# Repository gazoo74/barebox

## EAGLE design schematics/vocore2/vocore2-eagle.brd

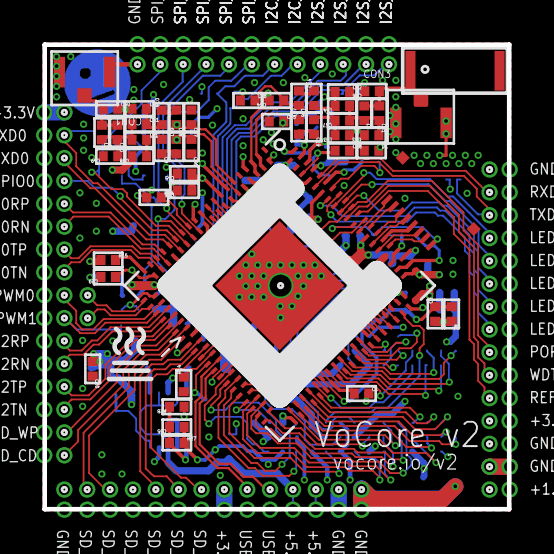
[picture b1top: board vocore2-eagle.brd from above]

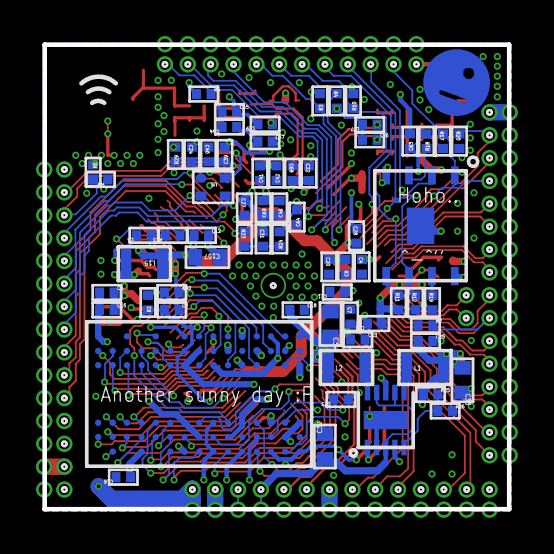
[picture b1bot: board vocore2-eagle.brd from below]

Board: 2 copper layers, 25.8 x 25.8 mm, 177 parts (68 on the bottom side), 129 nets.

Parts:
C1, C2, C3, C4, C5, C6, C7, C8, C9, C10, C11, C12, C13, C14, C15, C16, C18, C19, C20, C21, C22, C23, C24, C25, C27, C28, C29, C30, C31, C35, C36, C37, C38, C39, C40, C41, C42, C43, C44, C45, C46, C47, C48, C49, C50, C51, C52, C53, C54, C55, C56, C57, C60, C61, C63, C64, C65, C68, C69: 0402; 0402_1PRIMARY
C32, C33, C34, C107: 0603; 0603_1PRIMARY
CON1, CON3: SMA$2F$UFLR; SMA$2F$UFLR_1PRIMARY
CON2: 5020; 5020_1PRIMARY
D1: 0402; 0402_1PRIMARY
L1, L2, L15: 0806; 0806_1PRIMARY
L3, L5, L26, L27, L28, L29, L48, L49, L50, L51, L53, L54, L56, L57: 0402; 0402_1PRIMARY
LX01, LX02: PORT_1PIN_DECAL; PORT_1PIN_DECAL_1PRIMARY
PB00, PB01, PB02, PB03, PB04, PB05, PB06, PB07, PB08, PB09, PB10, PB11, PB12, PB13: PORT_1P5PIN_DECAL; PORT_1P5PIN_DECAL_1PRIMARY
PL00, PL01, PL02, PL03, PL04, PL05, PL06, PL07, PL08, PL09, PL10, PL11, PL12, PL13, PL14, PL15: PORT_1P5PIN_DECAL; PORT_1P5PIN_DECAL_1PRIMARY
PM00: PORT_1PIN_DECALDA; PORT_1PIN_DECALDA_1PRIMARY
PR00, PR01, PR02, PR03, PR04, PR05, PR06, PR07, PR08, PR09, PR10, PR11, PR12, PR13, PR14: PORT_1P5PIN_DECAL; PORT_1P5PIN_DECAL_1PRIMARY
PT00, PT01, PT02, PT03, PT04, PT05, PT06, PT07, PT08, PT09, PT10, PT11: PORT_1P5PIN_DECAL; PORT_1P5PIN_DECAL_1PRIMARY
R1, R2, R3, R4, R5, R6, R7, R9, R10, R11, R12, R13, R14, R15, R16, R17, R18, R19, R20, R23, R24, R25, R26, R27, R28, R29, R30: 0402; 0402_1PRIMARY
U1: MT7628AN$2F$DRQFN156$2F$SMD$2F$P0.5$2F$12X12; MT7628AN$2F$DRQFN156$2F$SMD$31PRIMARY
U2: BGA-84; BGA-84_1PRIMARY
U3: GD25Q128CW; GD25Q128CW_1PRIMARY
U4: TPS62410DRCR; TPS62410DRCR_1PRIMARY
U5: XTAL2520; XTAL2520_1PRIMARY
U8$2F$NC$2F$HIDE: FH19SC-8S-0.5SH; FH19SC-8S-0.5SH_1PRIMARY

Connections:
$$$4985: C10.2, C51.1, L50.1
$$$5344: C49.2, C51.2, C60.1, L3.1, L51.2
$$$5504: C14.2, C52.2, L54.1
$$$5505: C53.2, C57.2, C61.1, L5.1, L54.2
$$$21554: C2.2, C3.1, R1.2, R2.1, U1.90, U1.104, U2.50
$$$26111: C50.2, C60.2, CON1.1, L3.2
$$$26247: C9.1, L49.2
$$$26315: C10.1, L48.2
$$$26342: C56.2, C61.2, CON2.2, CON3.1, L5.2
$$$26483: C14.1, L56.2
$$$26503: C19.1, L57.2
$$$30241: C9.2, C48.2, L51.1
$$$30244: C19.2, C57.1, L53.1
+1.2V: C1.2, C7.2, C8.2, C11.2, C12.2, C13.2, C20.1, C27.2, C28.2, C107.2, L15.1, U1.22, U1.58, U1.89, U1.91, U1.122, U1.131, U1.145
+1.8V: C2.1, C6.2, C15.2, C16.2, C18.2, C34.1, C35.2, C41.2, C42.2, C43.2, C44.2, C45.2, C46.2, C47.2, C69.2, L2.1, PR14.1, PR14.2, R2.2, R27.1, R30.2, U1.15, U1.79, U1.98, U1.116, U1.149, U1.154, U1.155, U2.1, U2.6, U2.13, U2.15, U2.16, U2.18, U2.25, U2.30, U2.37, U2.39, U2.40, U2.42, U2.49, U2.54, U2.69, U2.80
+3.3V: C4.1, C5.2, C21.1, C22.2, C23.2, C24.2, C25.2, C29.2, C30.2, C33.2, C39.1, C40.2, C63.1, C64.2, C65.1, C68.2, L1.2, L26.2, L27.1, L28.2, L29.1, PB07.1, PB07.2, PL00.1, PL00.2, PR11.1, PR11.2, R3.2, R4.2, R9.2, R12.2, R13.1, R17.2, R18.2, R19.2, R24.2, R25.2, U1.8, U1.14, U1.23, U1.32, U1.38, U1.41, U1.53, U1.60, U1.117, U1.123, U1.124, U1.134, U1.146, U1.150, U3.8, U4.4
+5V: C32.2, PB12.1, PB12.2, PB13.1, PB13.2, U4.3, U4.7, U4.9
DCDC_ADJ2: C35.1, R27.2, R28.1, U4.1
DCDC_DEF1: R25.1, R26.2, U4.5
DCDC_SW1: L1.1, U4.6
DCDC_SW2: L2.2, U4.10
DDR2_A0: U1.80, U2.68
DDR2_A1: U1.88, U2.66
DDR2_A2: U1.87, U2.67
DDR2_A3: U1.97, U2.71
DDR2_A4: U1.82, U2.74
DDR2_A5: U1.93, U2.72
DDR2_A6: U1.86, U2.73
DDR2_A7: U1.95, U2.75
DDR2_A8: U1.84, U2.78
DDR2_A9: U1.94, U2.76
DDR2_A10: U1.92, U2.65
DDR2_A11: U1.85, U2.77
DDR2_A12: U1.96, U2.81
DDR2_A13: U1.83, U2.84
DDR2_BA0: U1.100, U2.61
DDR2_BA1: U1.99, U2.62
DDR2_BA2: U1.101, U2.60
DDR2_CAS: U1.75, U2.63
DDR2_CKE: U1.103, U2.55
DDR2_CLK: U1.77, U2.53
DDR2_CLKN: U1.76, U2.58
DDR2_CS: U1.78, U2.64
DDR2_LDM: U1.108, U2.33
DDR2_LDQS: U1.113, U2.34
DDR2_MD0: U1.71, U2.41
DDR2_MD1: U1.107, U2.38
DDR2_MD2: U1.69, U2.46
DDR2_MD3: U1.105, U2.45
DDR2_MD4: U1.106, U2.43
DDR2_MD5: U1.73, U2.48
DDR2_MD6: U1.109, U2.31
DDR2_MD7: U1.70, U2.36
DDR2_MD8: U1.66, U2.17
DDR2_MD9: U1.112, U2.14
DDR2_MD10: U1.68, U2.22
DDR2_MD11: U1.110, U2.21
DDR2_MD12: U1.111, U2.19
DDR2_MD13: U1.67, U2.24
DDR2_MD14: U1.114, U2.7
DDR2_MD15: U1.65, U2.12
DDR2_ODT: U1.74, U2.59
DDR2_RAS: U1.81, U2.57
DDR2_UDM: U1.64, U2.9
DDR2_UDQS: U1.72, U2.10
DDR2_WE: U1.102, U2.56
DDRLDO18V: R30.1, U1.125
EPHY_VRT: R15.1, U1.39
FLASH_HOLD: R19.1, U3.7
FLASH_WP: R18.1, U3.3
GND: C1.1, C3.2, C4.2, C5.1, C6.1, C7.1, C8.1, C11.1, C12.1, C13.1, C15.1, C16.1, C18.1, C20.2, C21.2, C22.1, C23.1, C24.1, C25.1, C27.1, C28.1, C29.1, C30.1, C31.1, C32.1, C33.1, C34.2, C36.1, C37.2, C38.1, C39.2, C40.1, C41.1, C42.1, C43.1, C44.1, C45.1, C46.1, C47.1, C48.1, C49.1, C50.1, C52.1, C53.1, C54.1, C55.2, C56.1, C63.2, C64.1, C65.2, C68.1, C69.1, C107.1, CON1.2, CON1.3, CON3.2, CON3.3, D1.2, L50.2, L53.2, PB00.1, PB00.2, PB10.1, PB10.2, PB11.1, PB11.2, PM00.1, PR00.1, PR00.2, PR12.1, PR12.2, PR13.1, PR13.2, PT00.1, PT00.2, R1.1, R5.2, R6.2, R7.2, R10.2, R11.2, R14.2, R15.2, R20.2, R26.1, R28.2, U1.1, U1.2, U1.7, U1.10, U1.13, U1.63, U1.115, U1.120, U1.121, U1.128, U1.152, U1.156, U1.157, U2.3, U2.4, U2.8, U2.11, U2.20, U2.23, U2.27, U2.28, U2.32, U2.35, U2.44, U2.47, U2.51, U2.52, U2.70, U2.79, U3.4, U3.9, U4.2, U4.8, U4.11, U5.2, U5.3, U5.4
GPIO0: PL03.1, PL03.2, U1.29
I2C_CLK: PT07.1, PT07.2, R3.1, U1.20
I2C_SD: PT06.1, PT06.2, R4.1, U1.21
I2S_CLK: PT08.1, PT08.2, U1.19
I2S_SDI: PT10.1, PT10.2, U1.16
I2S_SDO: PT11.1, PT11.2, R5.1, U1.17
I2S_WS: PT09.1, PT09.2, U1.18
LED0: PR06.1, PR06.2, U1.143
LED1: PR07.1, PR07.2, U1.142
LED2: PR03.1, PR03.2, U1.141
LED3: PR04.1, PR04.2, U1.140
LED4: PR05.1, PR05.2, U1.139
LXBK: L15.2, U1.118, U1.119
MDI_P0RN: PL05.1, PL05.2, U1.34
MDI_P0RP: PL04.1, PL04.2, U1.33
MDI_P0TN: PL07.1, PL07.2, U1.36
MDI_P0TP: PL06.1, PL06.2, U1.35
MDI_P1RN: PL09.1, PL09.2, R7.1, U1.44
MDI_P1RP: PL08.1, PL08.2, U1.43
MDI_P1TN: LX02.1, U1.42
MDI_P1TP: LX01.1, U1.40
MDI_P2RN: PL11.1, PL11.2, U1.46
MDI_P2RP: PL10.1, PL10.2, U1.45
MDI_P2TN: PL13.1, PL13.2, U1.48
MDI_P2TP: PL12.1, PL12.2, U1.47
MDI_P3RN: PB02.1, PB02.2, U1.52
MDI_P3RP: PB01.1, PB01.2, U1.51
MDI_P3TN: PL15.1, PL15.2, U1.50
MDI_P3TP: PL14.1, PL14.2, U1.49
MDI_P4RN: PB04.1, PB04.2, U1.55
MDI_P4RP: PB03.1, PB03.2, U1.54
MDI_P4TN: PB06.1, PB06.2, U1.57
MDI_P4TP: PB05.1, PB05.2, U1.56
PERST_N: R13.2, U1.135
PORST: PR08.1, PR08.2, R23.1, U1.138
PORST_M: C31.2, R23.2, R24.1
REFCLK: PR10.1, PR10.2, U1.136
SPI_CLK: PT02.1, PT02.2, R12.1, R16.2, U3.6
SPI_CLK_O: R16.1, U1.25
SPI_CS0: PT01.1, PT01.2, R17.1, U1.28, U3.1
SPI_CS1: PT05.1, PT05.2, R10.1, U1.24
SPI_MISO: PT03.1, PT03.2, U1.26, U3.2
SPI_MOSI: PT04.1, PT04.2, R11.1, U1.27, U3.5
UART_RXD0: PL02.1, PL02.2, U1.31
UART_RXD1: PR01.1, PR01.2, U1.148
UART_TXD0: PL01.1, PL01.2, R20.1, U1.30
UART_TXD1: PR02.1, PR02.2, R6.1, R9.1, U1.147
USB_DM: PB09.1, PB09.2, U1.62
USB_DP: PB08.1, PB08.2, U1.61
USB_VRT: R14.1, U1.59
WDTRST: PR09.1, PR09.2, U1.137
WF0_RFION: C55.1, L29.2, L57.1, U1.3, U1.4
WF0_RFIOP: C54.2, L28.1, L56.1, U1.5, U1.6
WF1_RFION: C37.1, L27.2, L48.1, U1.11
WF1_RFIOP: C36.2, L26.1, L49.1, U1.12
WLED_M: D1.1, R29.2
WLED_O: R29.1, U1.144
XTALIN: C38.2, U1.151, U5.1

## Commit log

2018-10-17 MIPS: add Vonger VoCore2 board
    This board is based on Mediatek mt7628an SoC.
2018-10-17 MIPS: start.S: split ERL reset from mips_disable_interrupts
    Currently, we cannot restart barebox from a bootloader. In macro
    mips_disable_interrupts we try to mask ST0_ERL. This flag is set by the
    CPU after a reset.
    When this Error Level flag is not set and we try to mask it, barebox
    stops to run without any further traces.
    To avoid such situation, we mask this flag in a dedicated macro.
2018-10-17 debug_ll: add GETC_LL and TSTC_LL functions
2018-10-17 MIPS: mt7628: register debug-ll console
2018-10-17 MIPS: mt7628: add uartlite
2018-10-17 datasheet: add vocore2 documents
    Downloaded from here[1] and there[2].
    [1]: http://vonger.cn/misc/vocore2/datasheet.zip
    [2]: http://vonger.cn/misc/vocore2/source.zip
2018-10-17 MIPS: mt7628: make debug ll uartlite selectable
2018-10-17 Add low-level ns16550 serial driver
2018-10-17 MIPS: vocore2: add pbl image support
2018-10-17 startup: print banner lines for loglevel info and higher
    This commit prevents from printing *ONLY* empty lines when loglevel is
    set below the notice level.
    The banner is printed with four empty lines at loglevel info (and
    higher) *OR* the banner is not print at all.
2018-10-17 datasheet: vocore2: add Micron M25P80 Serial Flash Embedded Memory
2018-10-17 datasheet: import MIPS Architecture for Programmers
    MIPS32 Architecture For Programmers
    Volume I: Introduction to the MIPS32 Architecture
    Volume II: The MIPS32 Instruction Set
    Volume III: The MIPS32 Privileged Resource Architecture
2018-10-17 datasheet: vocore2: import schematics
2018-10-17 MIPS: vocore2: select r4k clocksource library
    This provides a real clock source and removes the following warning.
    Warning: Using dummy clocksource
2018-10-17 datasheet: vocore2: move pdf to components subdir
2018-10-17 datasheet: mips: move pdf to mips subdir
2018-10-17 MIPS: vocore2: set appropriate hpt frequency
    According to vocore.io[1], the CPU runs at 580MHz.
    [1]: https://vocore.io/v2.html
2018-10-17 MIPS: mediatek: add restart handler
2018-10-17 MIPS: csrc-r4k: add hpt frequency option
    This sets a specific value for the HPT frequency without the need of
    using a device-tree.
2018-10-17 MIPS: vocore2: add reset and sleep commands
2018-10-17 MIPS: vocore2: add dmesg command
2019-12-09 HACK: Force dtb pointer to NULL
    This is a quick hack to force to use the built-in dtb (that is pointed
    by __dtb_start, later in the code) instead of using the one pointed by
    a0, that is 1 and causes the error below.
    Fixes:
    ## Starting application at 0x80100000 ...
    Ooops, address error on load or ifetch!
2019-12-09 fixup! MIPS: vocore2: add pbl image support
2019-12-09 fixup! MIPS: add Vonger VoCore2 board
